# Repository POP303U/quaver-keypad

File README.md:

# quaver-keypad
open source keypad for 4k-rhythm games

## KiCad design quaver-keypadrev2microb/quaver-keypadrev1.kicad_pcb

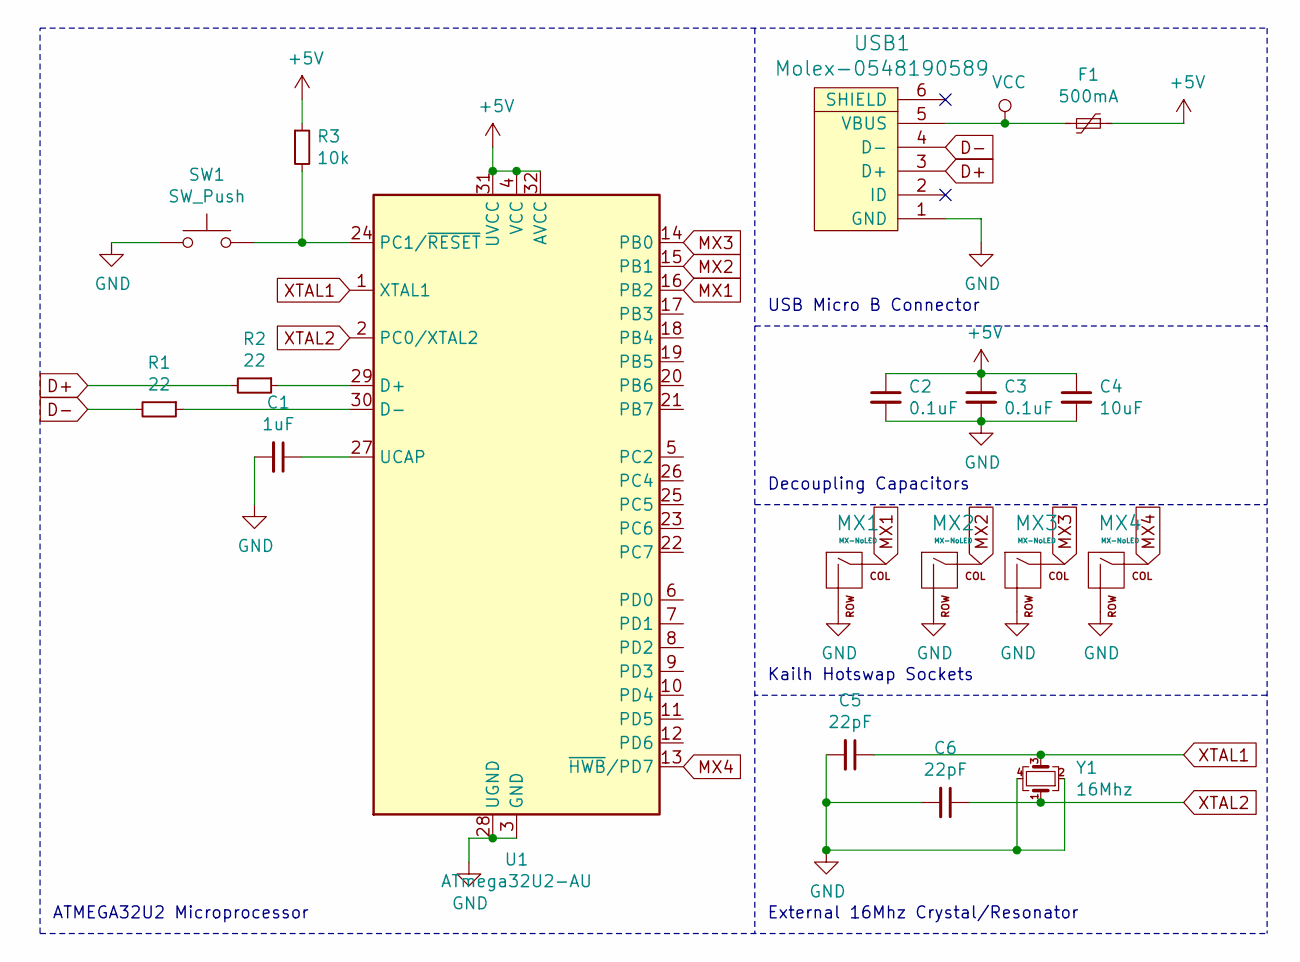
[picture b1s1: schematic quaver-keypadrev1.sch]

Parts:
C1: 1uF; C_0805_2012Metric
C2, C3: 0.1uF; C_0805_2012Metric
C4: 10uF; C_0805_2012Metric
C5, C6: 22pF; C_0805_2012Metric
F1: 500mA; Fuse_1206_3216Metric
MX1, MX2, MX3, MX4: MX-NoLED; Kailh_socket_MX
R1, R2: 22; R_0805_2012Metric
R3: 10k; R_0805_2012Metric
SW1: SW_Push; SKQG-1155865
U1: ATmega32U2-AU; TQFP-32_7x7mm_P0.8mm
USB1: Molex-0548190589
Y1: 16Mhz; Crystal_SMD_3225-4Pin_3.2x2.5mm

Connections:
+5V: C2.1, C3.1, C4.1, F1.1, R3.1, U1.4 (VCC), U1.31 (UVCC), U1.32 (AVCC)
D+: R2.2, USB1.3 (D+)
D-: R1.2, USB1.4 (D-)
GND: C1.2, C2.2, C3.2, C4.2, C5.2, C6.2, MX1.2 (ROW), MX2.2 (ROW), MX3.2 (ROW), MX4.2 (ROW), SW1.1, U1.3 (GND), U1.28 (UGND), USB1.1 (GND), Y1.2, Y1.4
MX1: MX1.1 (COL), U1.16 (PB2)
MX2: MX2.1 (COL), U1.15 (PB1)
MX3: MX3.1 (COL), U1.14 (PB0)
MX4: MX4.1 (COL), U1.13 (~HWB~/PD7)
unnamed: C1.1, U1.27 (UCAP)
unnamed: R1.1, U1.30 (D-)
unnamed: R2.1, U1.29 (D+)
unnamed: R3.2, SW1.2, U1.24 (PC1/~RESET)
VCC: F1.2, USB1.5 (VBUS)
XTAL1: C5.1, U1.1 (XTAL1), Y1.3
XTAL2: C6.1, U1.2 (PC0/XTAL2), Y1.1

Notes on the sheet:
ATMEGA32U2 Microprocessor
USB Micro B Connector
Decoupling Capacitors
External 16Mhz Crystal/Resonator
Kailh Hotswap Sockets

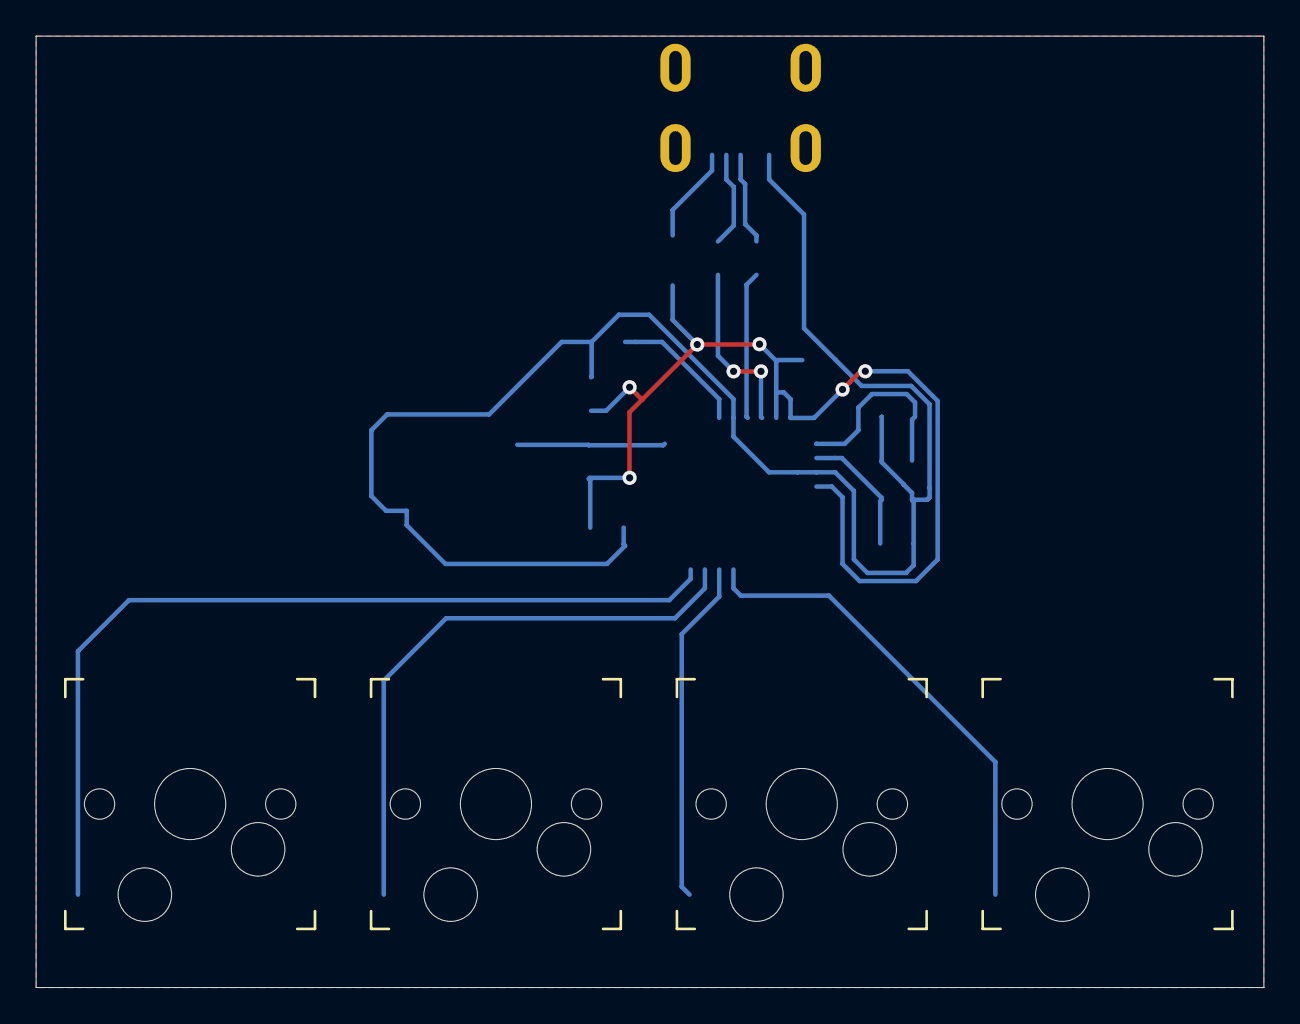
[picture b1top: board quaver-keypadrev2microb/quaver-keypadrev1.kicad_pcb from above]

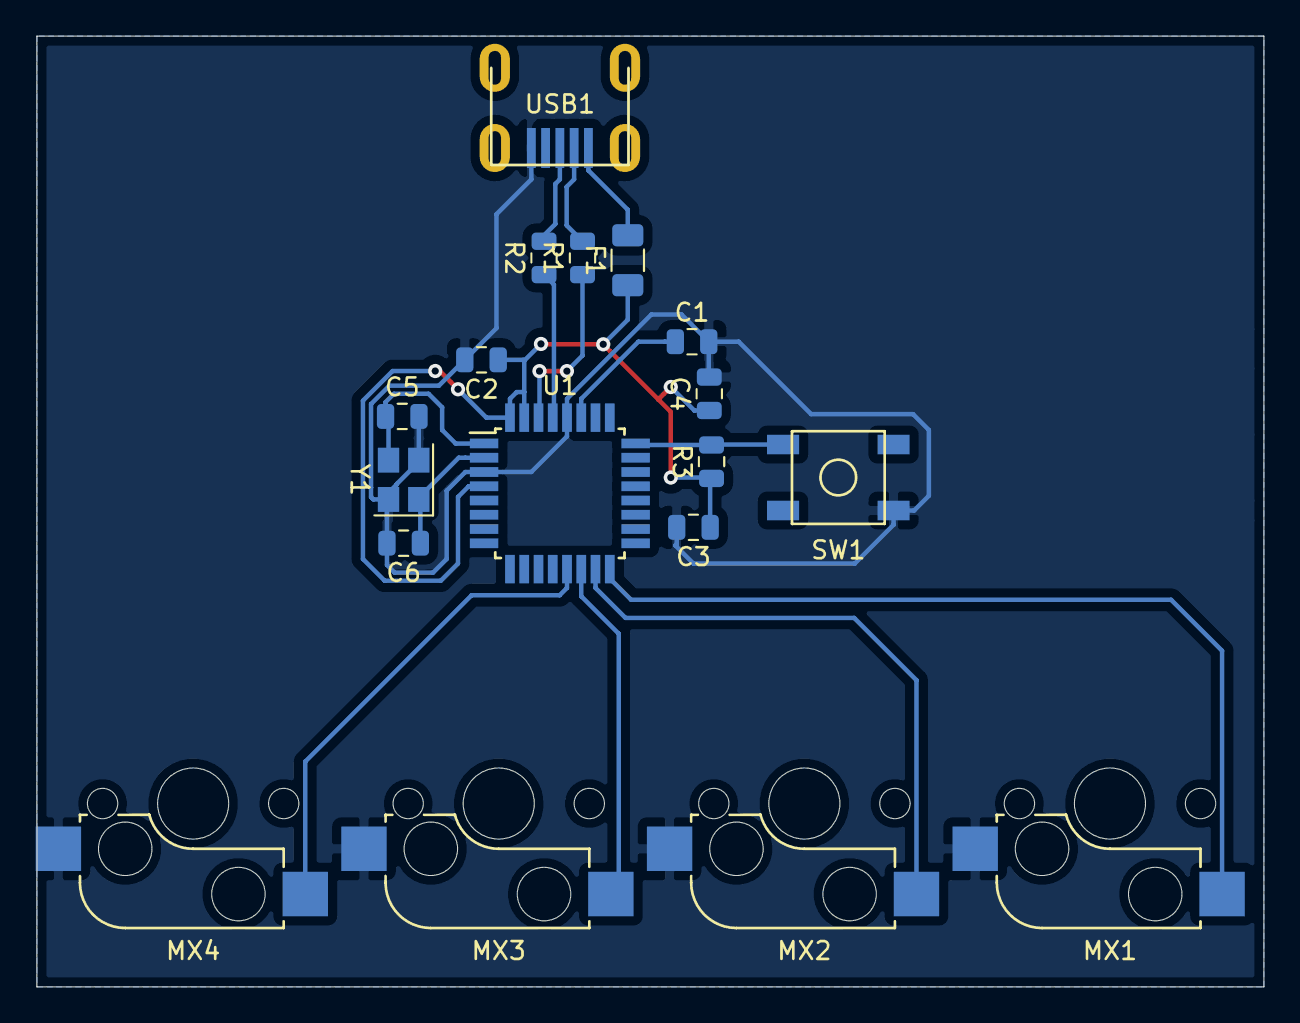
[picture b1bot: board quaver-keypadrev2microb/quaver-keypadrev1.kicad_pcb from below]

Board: 2 copper layers, 68.8 x 53.3 mm, 18 parts (14 on the bottom side), 15 nets.

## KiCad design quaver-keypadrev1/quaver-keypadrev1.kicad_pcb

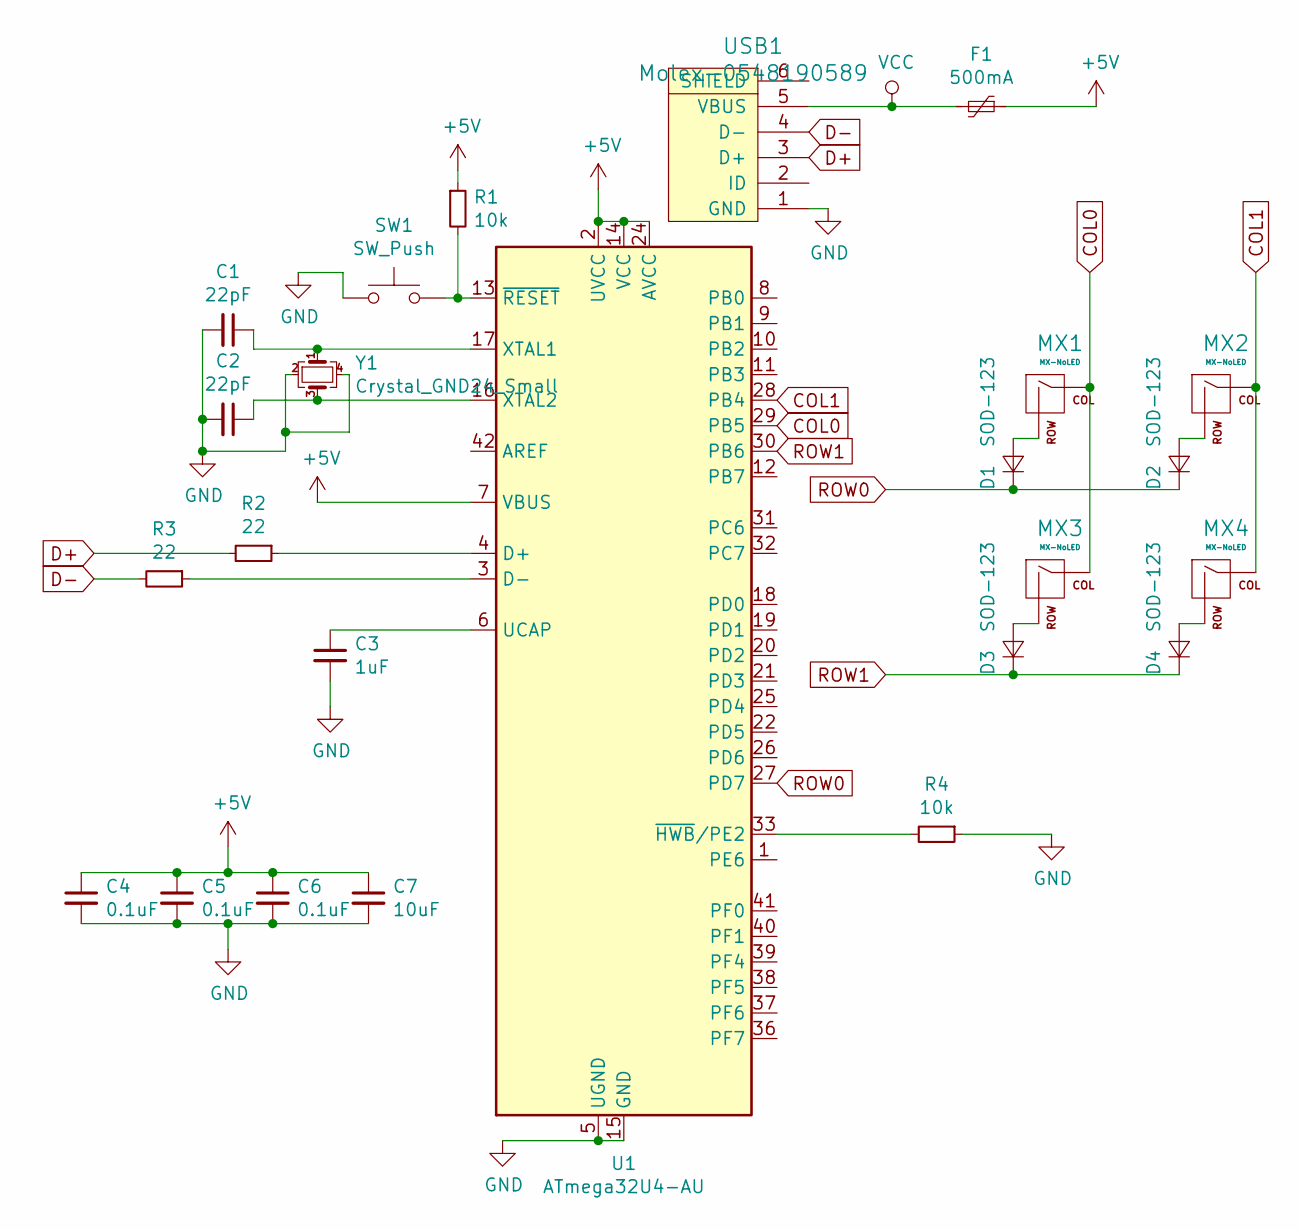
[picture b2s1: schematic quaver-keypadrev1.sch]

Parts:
C1, C2: 22pF; C_0805_2012Metric
C3: 1uF; C_0805_2012Metric
C4, C5, C6: 0.1uF; C_0805_2012Metric
C7: 10uF; C_0805_2012Metric
D1, D2, D3, D4: SOD-123; D_SOD-123
F1: 500mA; Fuse_1206_3216Metric
MX1, MX2, MX3, MX4: MX-NoLED; MX-1U
R1, R4: 10k; R_0805_2012Metric
R2, R3: 22; R_0805_2012Metric
SW1: SW_Push; SKQG-1155865
U1: ATmega32U4-AU; TQFP-44_10x10mm_P0.8mm
USB1: Molex-0548190589
Y1: Crystal_GND24_Small; Crystal_SMD_3225-4Pin_3.2x2.5mm

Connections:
+5V: C4.1, C5.1, C6.1, C7.1, F1.1, R1.1, U1.2 (UVCC), U1.7 (VBUS), U1.14 (VCC), U1.24 (AVCC), U1.34 (VCC), U1.44 (AVCC)
COL0: MX1.1 (COL), MX3.1 (COL), U1.29 (PB5)
COL1: MX2.1 (COL), MX4.1 (COL), U1.28 (PB4)
D+: R2.2, USB1.3 (D+)
D-: R3.2, USB1.4 (D-)
GND: C1.2, C2.2, C3.2, C4.2, C5.2, C6.2, C7.2, R4.1, SW1.1, U1.5 (UGND), U1.15 (GND), U1.23 (GND), U1.35 (GND), U1.43 (GND), USB1.1 (GND), Y1.2, Y1.4
unnamed: C1.1, U1.17 (XTAL1), Y1.1
unnamed: C2.1, U1.16 (XTAL2), Y1.3
unnamed: C3.1, U1.6 (UCAP)
unnamed: D1.2 (A), MX1.2 (ROW)
unnamed: D2.2 (A), MX2.2 (ROW)
unnamed: D3.2 (A), MX3.2 (ROW)
unnamed: D4.2 (A), MX4.2 (ROW)
unnamed: R1.2, SW1.2, U1.13 (~RESET)
unnamed: R2.1, U1.4 (D+)
unnamed: R3.1, U1.3 (D-)
unnamed: R4.2, U1.33 (~HWB~/PE2)
ROW0: D1.1 (K), D2.1 (K), U1.27 (PD7)
ROW1: D3.1 (K), D4.1 (K), U1.30 (PB6)
VCC: F1.2, USB1.5 (VBUS)

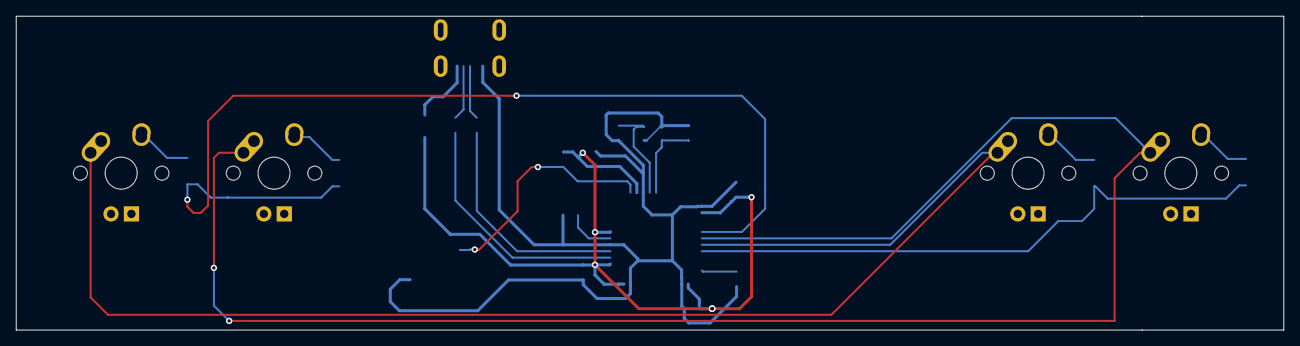
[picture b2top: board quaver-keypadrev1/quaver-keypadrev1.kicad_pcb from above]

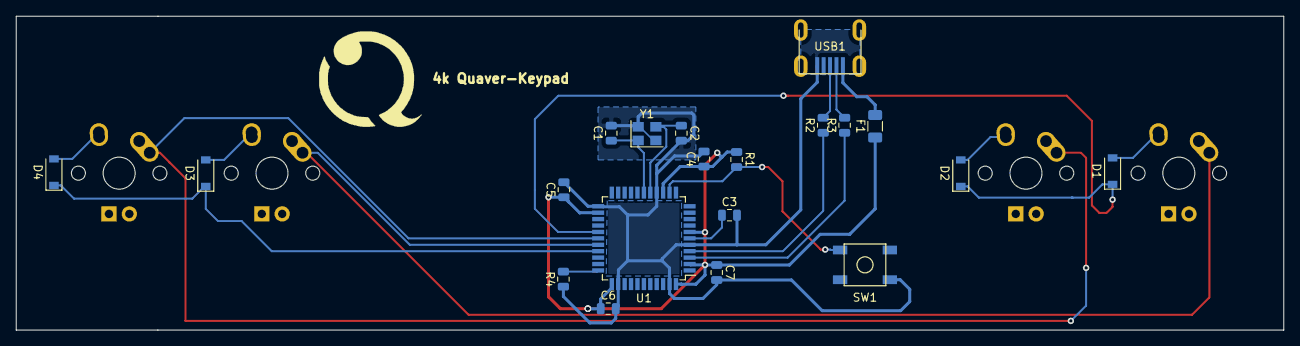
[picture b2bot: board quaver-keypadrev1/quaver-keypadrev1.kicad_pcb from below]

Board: 2 copper layers, 158.0 x 39.1 mm, 24 parts (20 on the bottom side), 20 nets.

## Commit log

2022-10-28 added basic files
2022-10-28 Add submodules
2022-10-28 add footprint libraries
2022-10-28 finished MCU schematic
2022-10-28 MCU schematic fix
2022-10-28 schematics finished
2022-10-29 fixed mx keys
2022-10-29 components placed
2022-10-29 finished general pcb
2022-10-30 finished 4k pcb + fixes
    the board should work now
2022-10-31 finished gerbers
    ready for delivery
2022-11-01 working on second revision
2022-11-02 finished schematic
    pls understand usb micro b bruh
2022-11-03 testing controller design
2022-11-04 added hotswap library
2022-11-05 made a quick learning board
    just made a board in 2 hours
